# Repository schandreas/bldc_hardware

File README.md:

This is a fork of Benjamin Vedders Open Source VESC project: https://github.com/vedderb/bldc-hardware

## Goals: 
The original Vesc design is very good for the things it wants to do. I want to do different things and still be able to use the same firmware. So I made this version.

The idea was that I only wanted to drive very weak motors. So this version is cheap and not that good. :man_shrugging:

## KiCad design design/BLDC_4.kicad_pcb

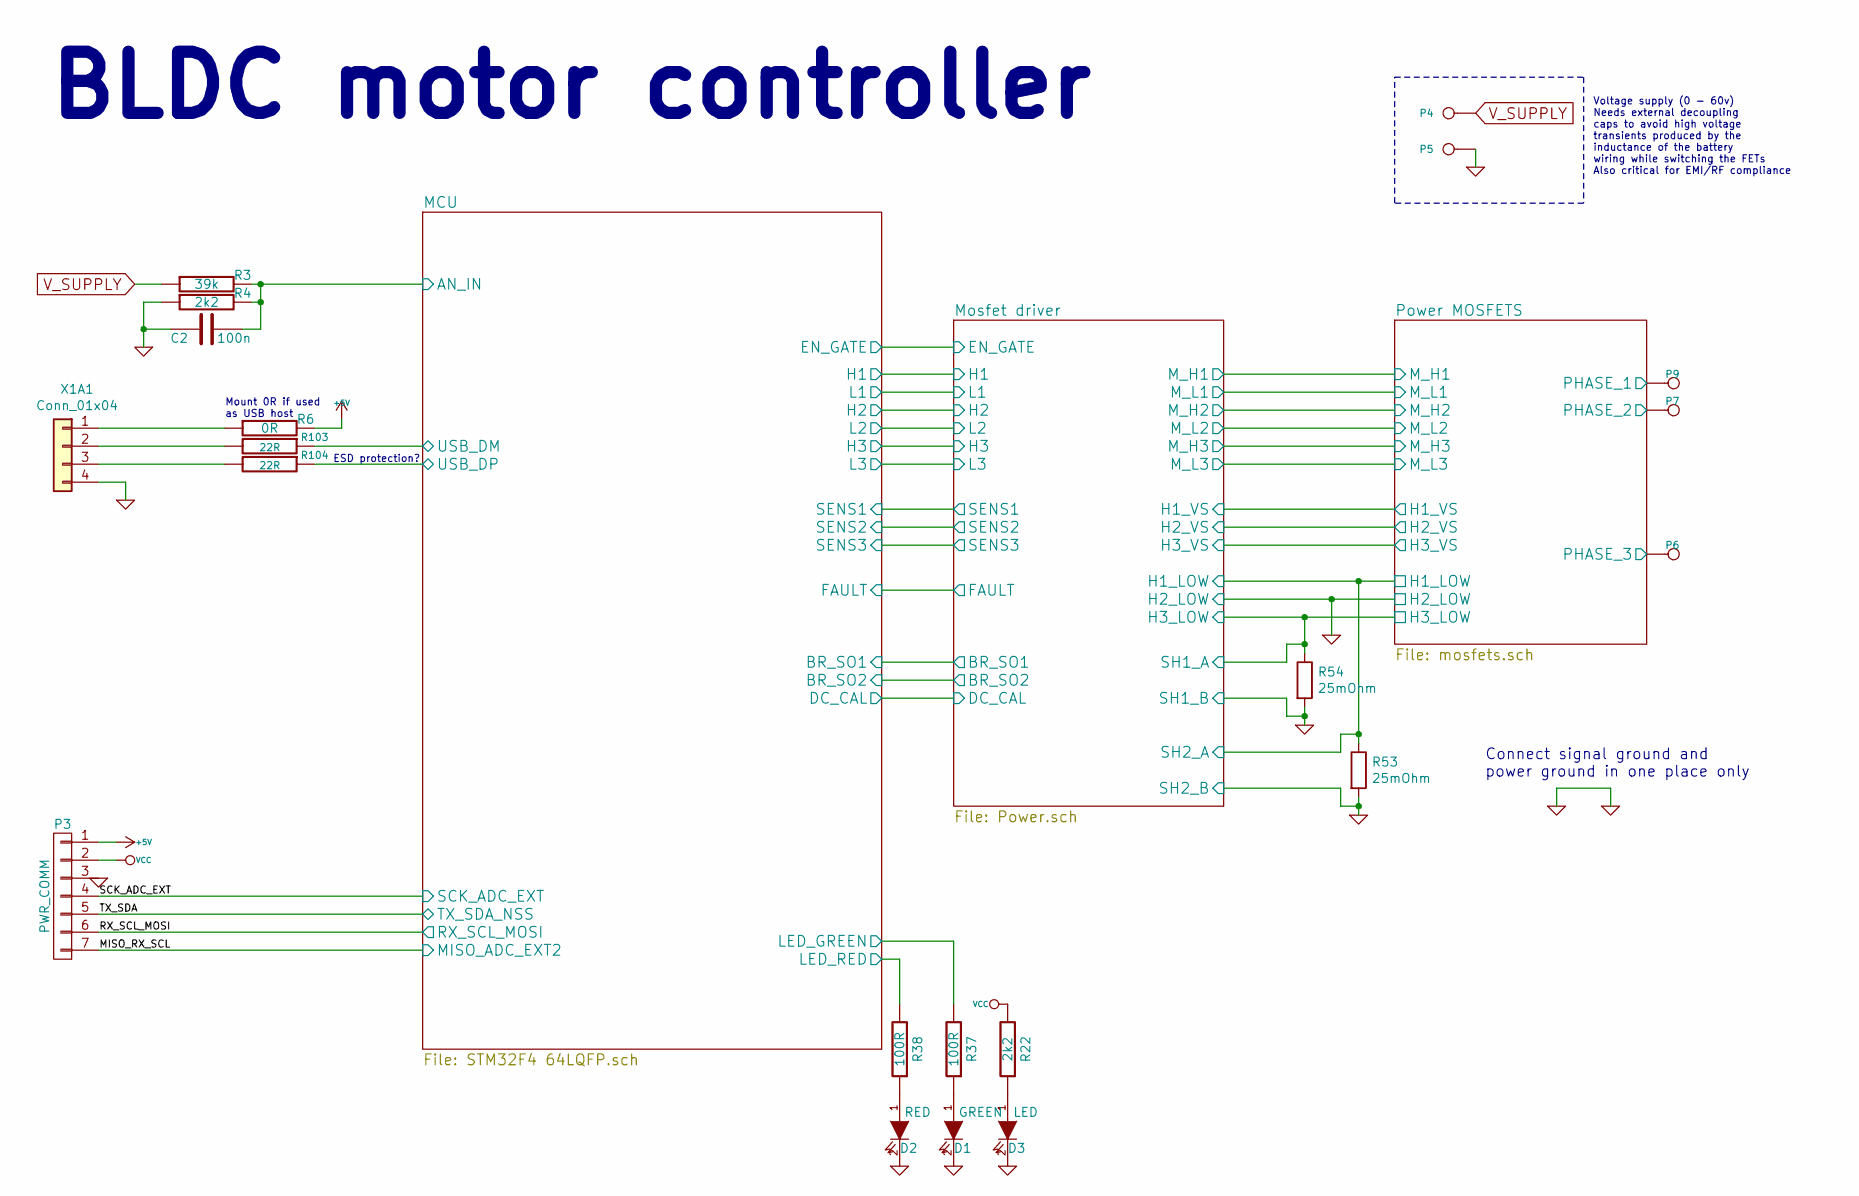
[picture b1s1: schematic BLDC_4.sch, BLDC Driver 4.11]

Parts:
C2: 100n; C_0603_1608Metric_Pad1.05x0.95mm_HandSolder
D1: GREEN; LED_0603_1608Metric
D2: RED; LED_0603_1608Metric
D3: LED; LED_0603_1608Metric
P3: PWR_COMM; JST_PH_B7B-PH-K_1x07_P2.00mm_Vertical
P4: IN+; 1PAD_4x5mm
P5: IN-; 1PAD_4x5mm
P6: MOTOR1; 1PAD_4x5mm
P7: MOTOR2; 1PAD_4x5mm
P9: MOTOR3; 1PAD_4x5mm
R3: 39k; R_0603_1608Metric
R4, R22: 2k2; R_0603_1608Metric
R6: 0R; R_0603_1608Metric
R37, R38: 100R; R_0603_1608Metric
R53, R54: 25mOhm; R_0612_1632Metric
R103, R104: 22R; R_0603_1608Metric
X1A1: Conn_01x04; PinHeader_1x04_P2.54mm_Vertical

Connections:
+5V: P3.1, R6.2; also elsewhere on the board
/MCU/AN_IN: C2.2, R3.2, R4.2; also elsewhere on the board
/MCU/LED_GREEN: R37.2; also elsewhere on the board
/MCU/LED_RED: R38.2; also elsewhere on the board
/MCU/USB_DM: R103.1; also elsewhere on the board
/MCU/USB_DP: R104.1; also elsewhere on the board
/MISO_RX_SCL: P3.7; also elsewhere on the board
/Mosfet driver/H1_LOW: R53.1; also elsewhere on the board
/Mosfet driver/H1_VS: P9.1; also elsewhere on the board
/Mosfet driver/H2_VS: P7.1; also elsewhere on the board
/Mosfet driver/H3_LOW: R54.1; also elsewhere on the board
/Mosfet driver/H3_VS: P6.1; also elsewhere on the board
/RX_SCL_MOSI: P3.6; also elsewhere on the board
/SCK_ADC_EXT: P3.4; also elsewhere on the board
/TX_SDA: P3.5; also elsewhere on the board
GND: C2.1, D1.2 (K), D2.2 (K), D3.2 (K), P3.3, P5.1, R4.1, R53.2, R54.2, X1A1.4; also elsewhere on the board
unnamed: D1.1 (A), R37.1
unnamed: D2.1 (A), R38.1
unnamed: D3.1 (A), R22.1
unnamed: R6.1, X1A1.1
unnamed: R103.2, X1A1.2
unnamed: R104.2, X1A1.3
VCC: P3.2, R22.2; also elsewhere on the board
V_SUPPLY: P4.1, R3.1; also elsewhere on the board

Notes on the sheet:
Mount 0R if used as USB host
ESD protection?
BLDC motor controller
Voltage supply (0 - 60v) Needs external decoupling caps to avoid high voltage transients produced by the inductance of the battery wiring while switching the FETs Also critical for EMI/RF compliance
Connect signal ground and power ground in one place only

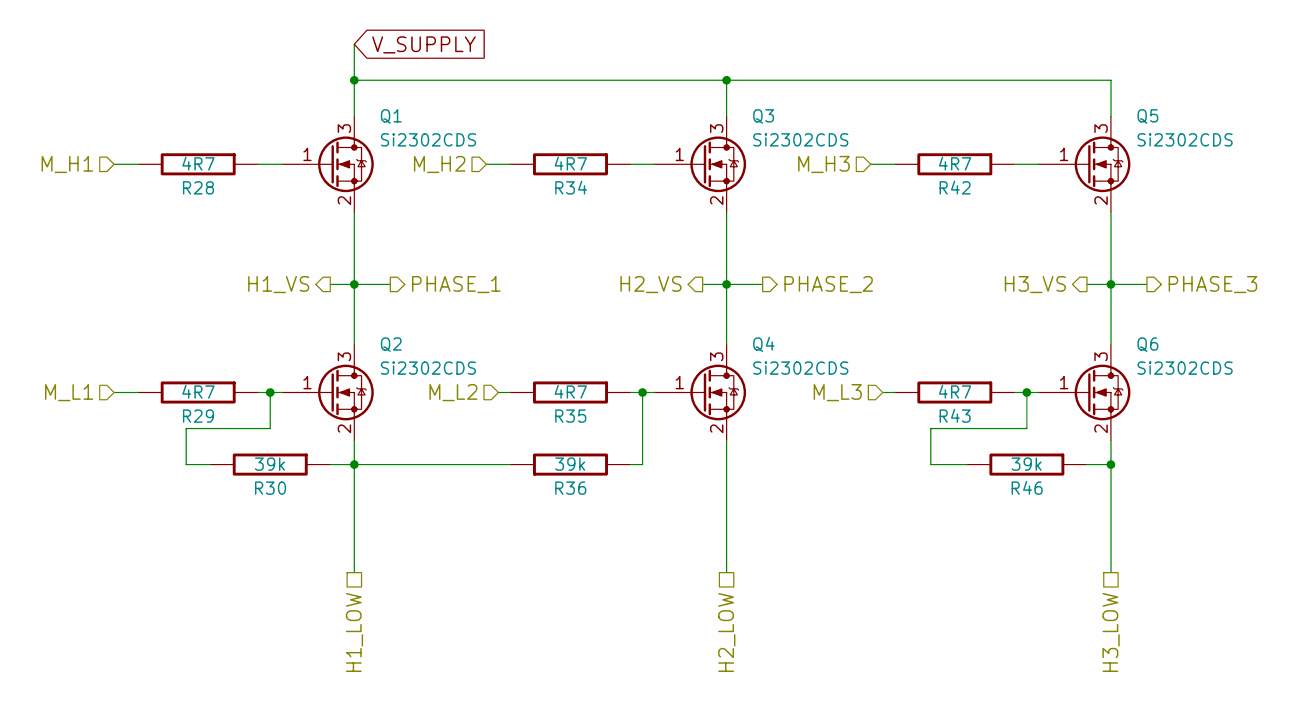
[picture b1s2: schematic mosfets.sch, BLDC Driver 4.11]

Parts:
Q1, Q2, Q3, Q4, Q5, Q6: Si2302CDS; SOT-23
R28, R29, R34, R35, R42, R43: 4R7; R_0603_1608Metric
R30, R36, R46: 39k; R_0603_1608Metric

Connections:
/Mosfet driver/H1_LOW: Q2.2 (S), R30.1, R36.1; also elsewhere on the board
/Mosfet driver/H1_VS: Q1.2 (S), Q2.3 (D); also elsewhere on the board
/Mosfet driver/H2_VS: Q3.2 (S), Q4.3 (D); also elsewhere on the board
/Mosfet driver/H3_LOW: Q6.2 (S), R46.1; also elsewhere on the board
/Mosfet driver/H3_VS: Q5.2 (S), Q6.3 (D); also elsewhere on the board
/Mosfet driver/M_H1: R28.2; also elsewhere on the board
/Mosfet driver/M_H2: R34.2; also elsewhere on the board
/Mosfet driver/M_H3: R42.2; also elsewhere on the board
/Mosfet driver/M_L1: R29.2; also elsewhere on the board
/Mosfet driver/M_L2: R35.2; also elsewhere on the board
/Mosfet driver/M_L3: R43.2; also elsewhere on the board
GND: Q4.2 (S); also elsewhere on the board
unnamed: Q1.1 (G), R28.1
unnamed: Q2.1 (G), R29.1, R30.2
unnamed: Q3.1 (G), R34.1
unnamed: Q4.1 (G), R35.1, R36.2
unnamed: Q5.1 (G), R42.1
unnamed: Q6.1 (G), R43.1, R46.2
V_SUPPLY: Q1.3 (D), Q3.3 (D), Q5.3 (D); also elsewhere on the board

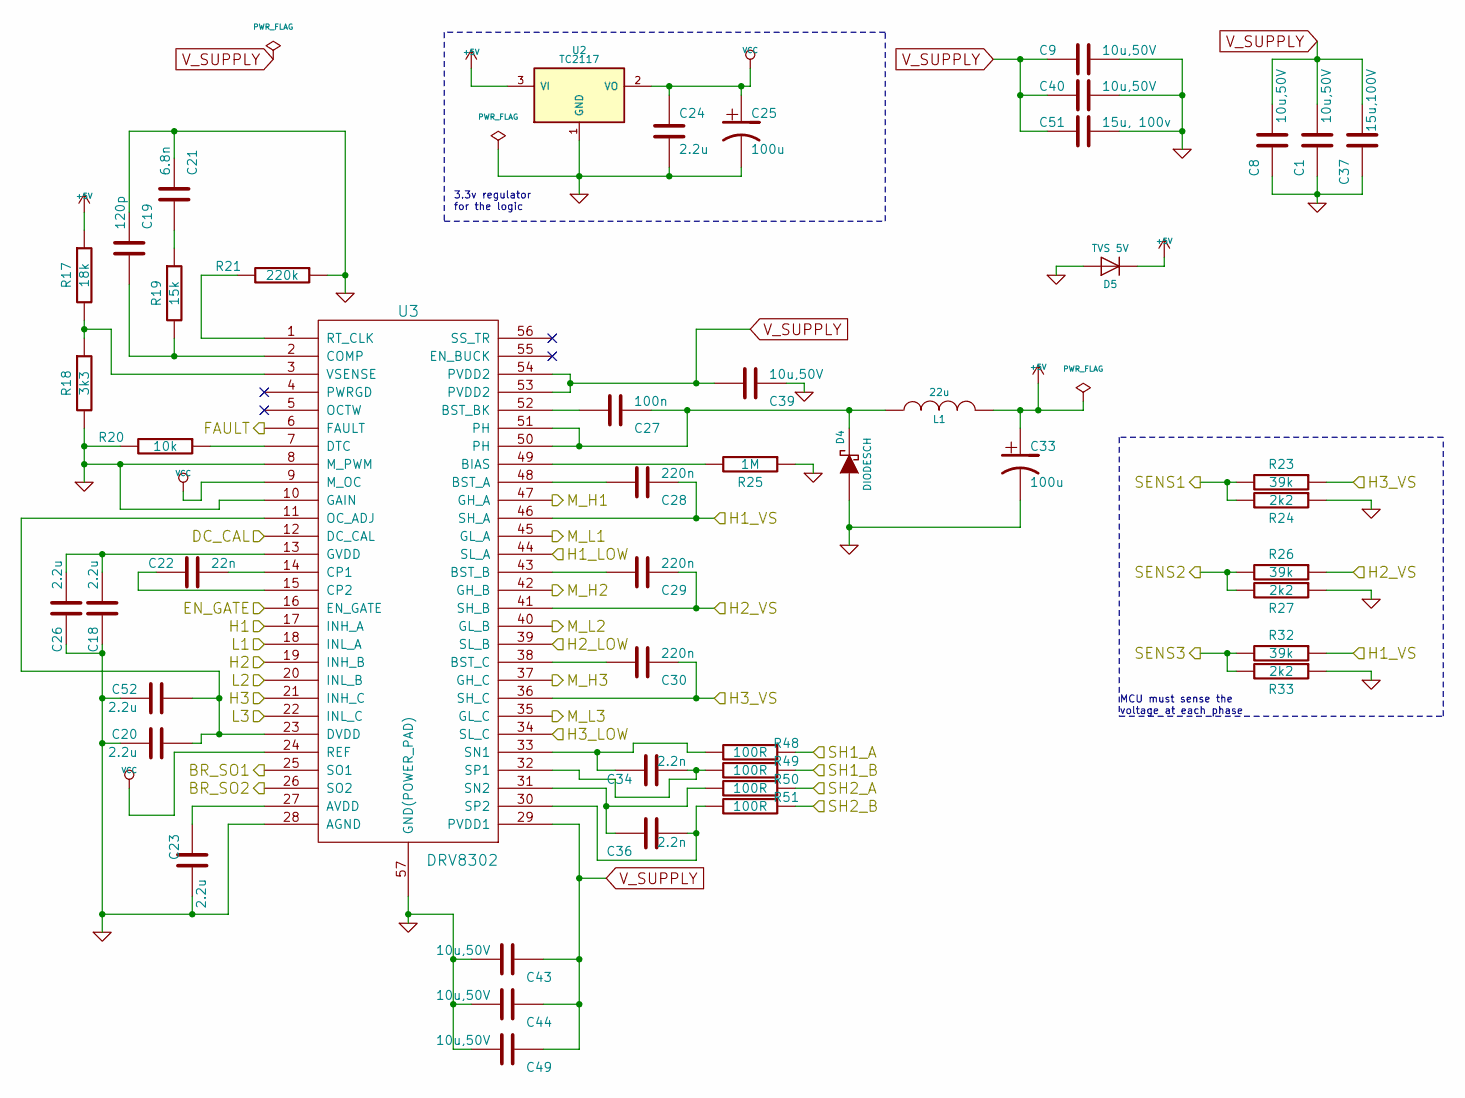
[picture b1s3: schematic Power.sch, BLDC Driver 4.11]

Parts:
C1, C8, C9, C39, C40, C43, C44, C49: 10u,50V; C_1206_3216Metric
C18, C20, C23, C24, C26, C52: 2.2u; C_0603_1608Metric_Pad1.05x0.95mm_HandSolder
C19: 120p; C_0603_1608Metric_Pad1.05x0.95mm_HandSolder
C21: 6.8n; C_0603_1608Metric_Pad1.05x0.95mm_HandSolder
C22: 22n; C_0603_1608Metric_Pad1.05x0.95mm_HandSolder
C25, C33: 100u; CP_EIA-3528-21_Kemet-B
C27: 100n; C_0603_1608Metric_Pad1.05x0.95mm_HandSolder
C28, C29, C30: 220n; C_0603_1608Metric_Pad1.05x0.95mm_HandSolder
C34, C36: 2.2n; C_0603_1608Metric_Pad1.05x0.95mm_HandSolder
C37: 15u,100V; C_2220_5650Metric
C51: 15u, 100v; C_2220_5650Metric
D4: DIODESCH; D_SMA_Handsoldering
D5: TVS 5V; D_SMA_Handsoldering
L1: 22u; inductor_smd_8x5mm
R17: 18k; R_0603_1608Metric
R18: 3k3; R_0603_1608Metric
R19: 15k; R_0603_1608Metric
R20: 10k; R_0603_1608Metric
R21: 220k; R_0603_1608Metric
R23, R26, R32: 39k; R_0603_1608Metric
R24, R27, R33: 2k2; R_0603_1608Metric
R25: 1M; R_0603_1608Metric
R48, R49, R50, R51: 100R; R_0603_1608Metric
U2: TC2117; SOT-223-3_TabPin2
U3: DRV8302; HTSSOP-56-1EP_6.1x14mm_P0.5mm_EP3.61x6.35mm

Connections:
+5V: C33.1, D5.1 (K), L1.2, R17.1, U2.3 (VI); also elsewhere on the board
/MCU/BR_SO1: U3.25 (SO1); also elsewhere on the board
/MCU/BR_SO2: U3.26 (SO2); also elsewhere on the board
/MCU/DC_CAL: U3.12 (DC_CAL); also elsewhere on the board
/MCU/EN_GATE: U3.16 (EN_GATE); also elsewhere on the board
/MCU/FAULT: U3.6 (FAULT); also elsewhere on the board
/MCU/H1: U3.17 (INH_A); also elsewhere on the board
/MCU/H2: U3.19 (INH_B); also elsewhere on the board
/MCU/H3: U3.21 (INH_C); also elsewhere on the board
/MCU/L1: U3.18 (INL_A); also elsewhere on the board
/MCU/L2: U3.20 (INL_B); also elsewhere on the board
/MCU/L3: U3.22 (INL_C); also elsewhere on the board
/MCU/SENS1: R23.2, R24.2; also elsewhere on the board
/MCU/SENS2: R26.2, R27.2; also elsewhere on the board
/MCU/SENS3: R32.2, R33.2; also elsewhere on the board
/Mosfet driver/H1_LOW: R50.1, U3.44 (SL_A); also elsewhere on the board
/Mosfet driver/H1_VS: C28.1, R32.1, U3.46 (SH_A); also elsewhere on the board
/Mosfet driver/H2_VS: C29.1, R26.1, U3.41 (SH_B); also elsewhere on the board
/Mosfet driver/H3_LOW: R48.1, U3.34 (SL_C); also elsewhere on the board
/Mosfet driver/H3_VS: C30.1, R23.1, U3.36 (SH_C); also elsewhere on the board
/Mosfet driver/M_H1: U3.47 (GH_A); also elsewhere on the board
/Mosfet driver/M_H2: U3.42 (GH_B); also elsewhere on the board
/Mosfet driver/M_H3: U3.37 (GH_C); also elsewhere on the board
/Mosfet driver/M_L1: U3.45 (GL_A); also elsewhere on the board
/Mosfet driver/M_L2: U3.40 (GL_B); also elsewhere on the board
/Mosfet driver/M_L3: U3.35 (GL_C); also elsewhere on the board
GND: C1.1, C8.1, C9.1, C18.2, C19.1, C20.1, C21.1, C23.1, C24.2, C25.2, C26.2, C33.2, C37.1, C39.1, C40.1, C43.2, C44.2, C49.2, C51.1, C52.1, D4.1 (A), D5.2 (A), R18.2, R20.2, R21.1, R24.1, R25.1, R27.1, R33.1, R49.1, R51.1, U2.1 (GND), U3.8 (M_PWM), U3.10 (GAIN), U3.28 (AGND), U3.39 (SL_B), U3.57 (GND(POWER_PAD)); also elsewhere on the board
unnamed: C18.1, C26.1, U3.13 (GVDD)
unnamed: C19.2, R19.2, U3.2 (COMP)
unnamed: C20.2, C52.2, U3.11 (OC_ADJ), U3.23 (DVDD)
unnamed: C21.2, R19.1
unnamed: C22.1, U3.14 (CP1)
unnamed: C22.2, U3.15 (CP2)
unnamed: C23.2, U3.27 (AVDD)
unnamed: C27.1, D4.2 (K), L1.1, U3.50 (PH), U3.51 (PH)
unnamed: C27.2, U3.52 (BST_BK)
unnamed: C28.2, U3.48 (BST_A)
unnamed: C29.2, U3.43 (BST_B)
unnamed: C30.2, U3.38 (BST_C)
unnamed: C34.1, R48.2, U3.33 (SN1)
unnamed: C34.2, R49.2, U3.32 (SP1)
unnamed: C36.1, R50.2, U3.31 (SN2)
unnamed: C36.2, R51.2, U3.30 (SP2)
unnamed: R17.2, R18.1, U3.3 (VSENSE)
unnamed: R20.1, U3.7 (DTC)
unnamed: R21.2, U3.1 (RT_CLK)
unnamed: R25.2, U3.49 (BIAS)
VCC: C24.1, C25.1, U2.2 (VO), U3.9 (M_OC), U3.24 (REF); also elsewhere on the board
V_SUPPLY: C1.2, C8.2, C9.2, C37.2, C39.2, C40.2, C43.1, C44.1, C49.1, C51.2, U3.29 (PVDD1), U3.53 (PVDD2), U3.54 (PVDD2); also elsewhere on the board

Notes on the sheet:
MCU must sense the voltage at each phase
3.3v regulator for the logic

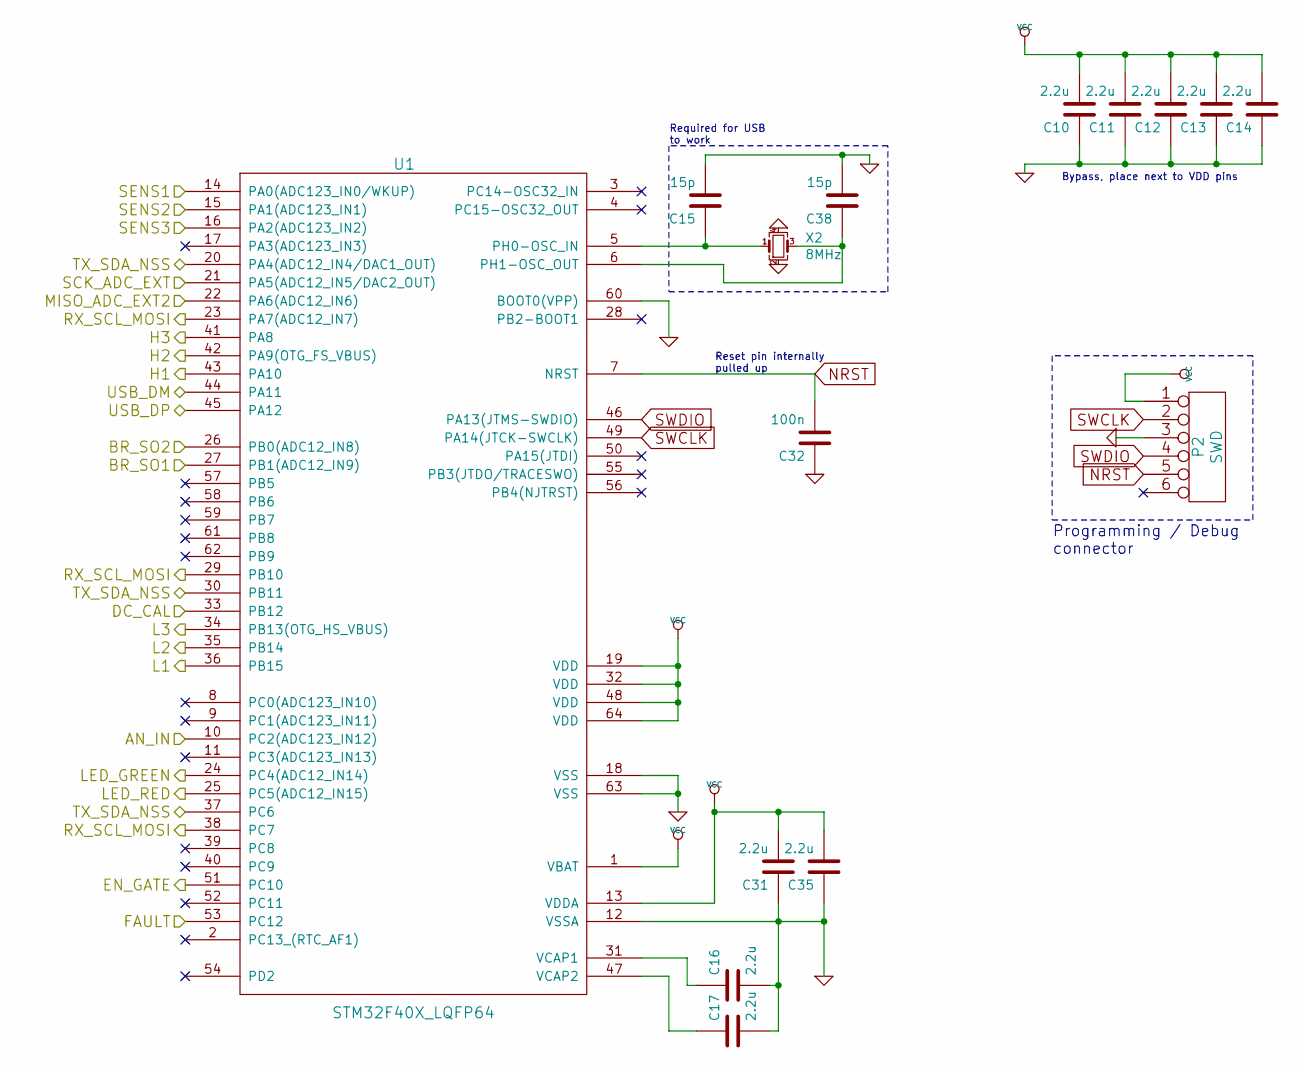
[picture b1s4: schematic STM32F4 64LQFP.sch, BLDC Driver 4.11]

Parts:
C10, C11, C12, C13, C14, C16, C17, C31, C35: 2.2u; C_0603_1608Metric
C15, C38: 15p; C_0603_1608Metric
C32: 100n; C_0603_1608Metric
P2: SWD; JST_PH_B6B-PH-K_1x06_P2.00mm_Vertical
U1: STM32F40X_LQFP64; LQFP-64_10x10mm_P0.5mm
X2: 8MHz; Crystal_SMD_Abracon_ABM3B-4Pin_5.0x3.2mm

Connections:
/MCU/AN_IN: U1.10 (PC2(ADC123_IN12)); also elsewhere on the board
/MCU/BR_SO1: U1.27 (PB1(ADC12_IN9)); also elsewhere on the board
/MCU/BR_SO2: U1.26 (PB0(ADC12_IN8)); also elsewhere on the board
/MCU/DC_CAL: U1.33 (PB12); also elsewhere on the board
/MCU/EN_GATE: U1.51 (PC10); also elsewhere on the board
/MCU/FAULT: U1.53 (PC12); also elsewhere on the board
/MCU/H1: U1.43 (PA10); also elsewhere on the board
/MCU/H2: U1.42 (PA9(OTG_FS_VBUS)); also elsewhere on the board
/MCU/H3: U1.41 (PA8); also elsewhere on the board
/MCU/L1: U1.36 (PB15); also elsewhere on the board
/MCU/L2: U1.35 (PB14); also elsewhere on the board
/MCU/L3: U1.34 (PB13(OTG_HS_VBUS)); also elsewhere on the board
/MCU/LED_GREEN: U1.24 (PC4(ADC12_IN14)); also elsewhere on the board
/MCU/LED_RED: U1.25 (PC5(ADC12_IN15)); also elsewhere on the board
/MCU/SENS1: U1.14 (PA0(ADC123_IN0/WKUP)); also elsewhere on the board
/MCU/SENS2: U1.15 (PA1(ADC123_IN1)); also elsewhere on the board
/MCU/SENS3: U1.16 (PA2(ADC123_IN2)); also elsewhere on the board
/MCU/USB_DM: U1.44 (PA11); also elsewhere on the board
/MCU/USB_DP: U1.45 (PA12); also elsewhere on the board
/MISO_RX_SCL: U1.22 (PA6(ADC12_IN6)); also elsewhere on the board
/RX_SCL_MOSI: U1.23 (PA7(ADC12_IN7)), U1.29 (PB10), U1.38 (PC7); also elsewhere on the board
/SCK_ADC_EXT: U1.21 (PA5(ADC12_IN5/DAC2_OUT)); also elsewhere on the board
/TX_SDA: U1.20 (PA4(ADC12_IN4/DAC1_OUT)), U1.30 (PB11), U1.37 (PC6); also elsewhere on the board
GND: C10.1, C11.1, C12.1, C13.1, C14.1, C15.2, C16.2, C17.2, C31.1, C32.1, C35.1, C38.2, P2.3, U1.12 (VSSA), U1.18 (VSS), U1.60 (BOOT0(VPP)), U1.63 (VSS), X2.2, X2.4; also elsewhere on the board
NRST: C32.2, P2.5, U1.7 (NRST)
unnamed: C15.1, U1.5 (PH0-OSC_IN), X2.1
unnamed: C16.1, U1.31 (VCAP1)
unnamed: C17.1, U1.47 (VCAP2)
unnamed: C38.1, U1.6 (PH1-OSC_OUT), X2.3
SWCLK: P2.2, U1.49 (PA14(JTCK-SWCLK))
SWDIO: P2.4, U1.46 (PA13(JTMS-SWDIO))
VCC: C10.2, C11.2, C12.2, C13.2, C14.2, C31.2, C35.2, P2.1, U1.1 (VBAT), U1.13 (VDDA), U1.19 (VDD), U1.32 (VDD), U1.48 (VDD), U1.64 (VDD); also elsewhere on the board

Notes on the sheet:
Programming / Debug connector
Reset pin internally pulled up
Required for USB to work
Bypass, place next to VDD pins

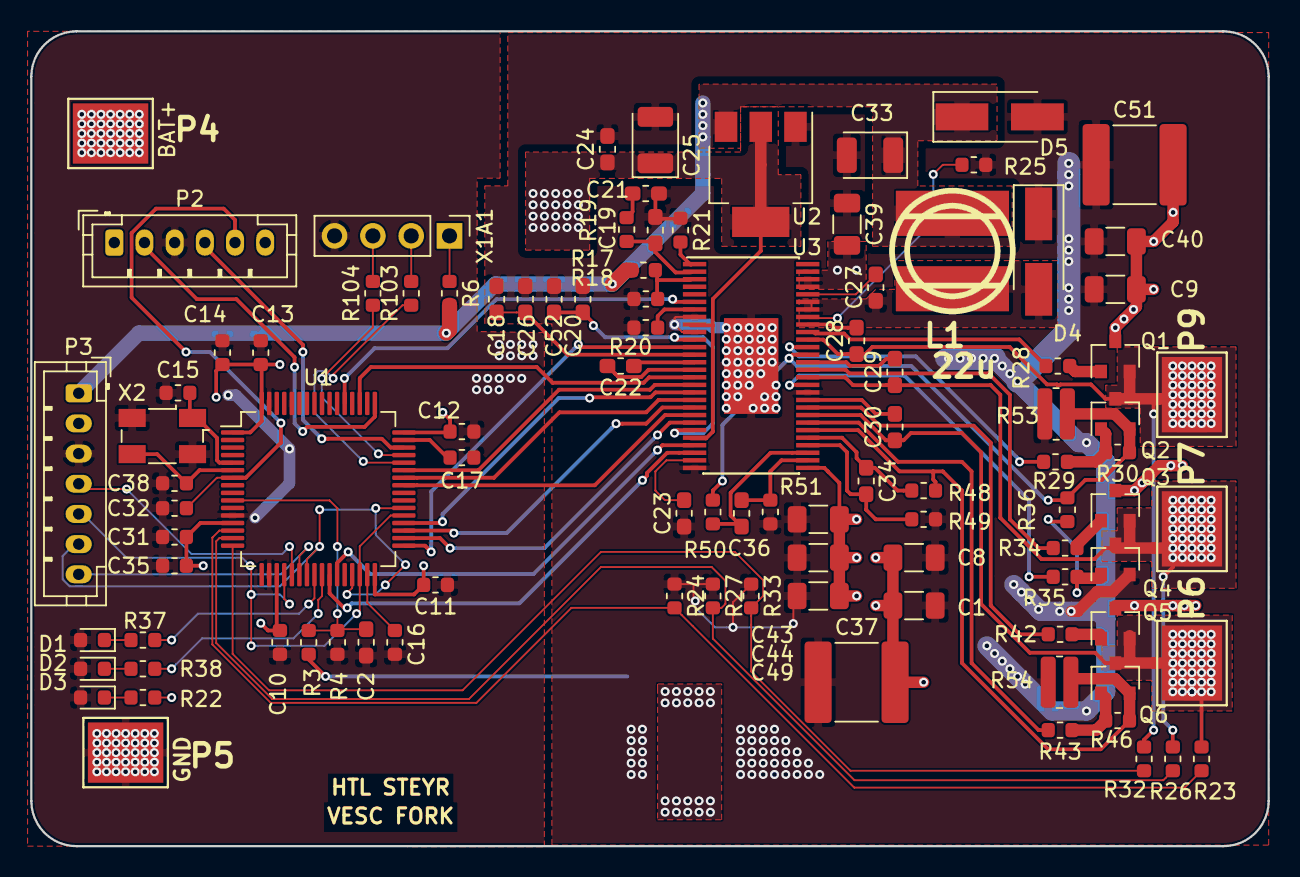
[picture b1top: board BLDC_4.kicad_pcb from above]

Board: 2 copper layers, 82.0 x 54.0 mm, 99 parts (0 on the bottom side), 77 nets.

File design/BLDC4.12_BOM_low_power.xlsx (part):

Part | Value | Package | Description | Qty | Place (YES/NO) | Distributor | Order Number | Comment | single price | multi price | link |  |  |  |  |  |  |  |  |  |  |  | LCSC
U1 |  | LQFP-64 | STM32F405RGT6 MCU | 1 | YES | RS | 746-8217 |  | 9.24 | 9.24 | https://at.rs-online.com/web/p/mikrocontroller/7468217/ |  |  |  |  |  |  |  |  |  |  |  | https://lcsc.com/product-detail/ST-Microelectronics_STMicroe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
U2 |  | SOT-223-3 | VREG | 1 | YES | RS | 823-4434 | moq 10 | 0.63300000000000001 | 0.63300000000000001 | https://at.rs-online.com/web/p/ldo-spannungsregler/8234434/ |  |  |  |  |  |  |  |  |  |  |  | https://lcsc.com/product-detail/Low-Dropout-Regulators-LDO_M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
U3 |  | HTSSOP-56-PP | MOSFET Driver | 1 | YES | RS | 762-0421 |  | 5.45 | 5.45 | https://at.rs-online.com/web/p/motor-treiber-ics/7620421/ |  |  |  |  |  |  |  |  |  |  |  | https://lcsc.com/product-detail/MOS-Drivers_TI_DRV8302DCA_DR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
L1 |  | inductor_smd_8x5mm | Power Inductor | 1 | YES | MOUSER | 652-SDR0805-220ML |  | 0.45 | 0.45 | https://www.mouser.at/ProductDetail/Bourns/SDR0805-220ML?qs=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
X1 |  | Conn_1x04 | Pinheader 1x04 2.54mm | 1 | YES | RS | 720-1310 | moq 10 | 0.22600000000000001 | 0.22600000000000001 | https://at.rs-online.com/web/p/leiterplatten-header/7201310/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
X2 | 8MHz | Crystal_5x3mm | Crystal 8MHz, 10PPM | 1 | YES | MOUSER | 815-ABM3B-8.0-10-1UT |  | 0.621 | 0.621 | https://www.mouser.at/ProductDetail/ABRACON/ABM3B-8000MHZ-10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 |  |  |  |  |  |  |  |  |  |  |  | https://lcsc.com/product-detail/Power-Inductors_BOURNS_SDR08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
Q1-Q6 | Si2302CDS | SOT-23 | MOSFET 20V 3A | 6 | YES | Farnell | 1684049 |  | 0.192 | 1.1520000000000001 | https://at.farnell.com/vishay/si2302cds-t1-ge3/mosfet-n-kana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
R53,R54 | 25mOhm | SMD-0612 | Shunt 25mOhm | 2 | YES | MOUSER | 652-CRK0612-FZ-R001E |  | 0.53 | 1.06 | https://www.mouser.at/ProductDetail/Bourns/CRK0612-FZ-R001E?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
D5 | 5V | DO-214AC-2 | TVS diode 5V | 1 | YES | MOUSER | 576-SMAJ5.0A |  | 0.36899999999999999 | 0.36899999999999999 | https://www.mouser.at/ProductDetail/Littelfuse/SMAJ50A?qs=%2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
D4 | 60V 2A | SOD-123W-2 | Shottky 60V 2A | 1 | YES | MOUSER | 771-PMEG6020ER-115 | Voltage and current important | 0.315 | 0.315 | https://www.mouser.at/ProductDetail/Nexperia/PMEG6020ER115?q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
C25,C33 | 100uF, 6.3V | c_tant_B | CAP 100u, 6.3V | 2 | YES | RS | 136-4122 | Voltage important, moq 25 | 0.442 | 0.88400000000000001 | https://at.rs-online.com/web/p/tantal-elektrolytkondensator/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
C1,C8,C9,C39,C40,C43,C44,C49 | 10uF 50V | SMD1206 | CAP 10u, 50V, 1206 | 8 | YES | MOUSER | 963-UMK316BBJ106ML-T | Voltage important, moq 10 | 0.31 | 2.48 | https://www.mouser.at/ProductDetail/Taiyo-Yuden/UMK316BBJ106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
C37,C51 | 15uF, 100V | SMD-2220 | CAP 15u, 100V, 2220 | 2 | YES | MOUSER | 810-CGA9P3X7S2A156M | Voltage important | 3.24 | 6.48 | https://www.mouser.at/ProductDetail/TDK/CGA9P3X7S2A156M250KB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
C2,C27,C32 | 100nF, 50V | SMD-0603 | CAP 100n, 50V, 0603 | 3 | YES | MOUSER | 581-06035C104JAT2A | Voltage important | 0.13500000000000001 | 0.40500000000000003 | https://www.mouser.at/ProductDetail/AVX/06035C104JAT2A?qs=%2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
C28,C29,C30 | 220nF,25V | SMD-0603 | CAP 220n, 25V, 0603 | 3 | YES | MOUSER | 963-TMK107B7224KA-T | Voltage important | 9.9000000000000005E-2 | 0.29700000000000004 | https://www.mouser.at/ProductDetail/Taiyo-Yuden/TMK107B7224K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
C24,C10,C11,C12,C13,C14,C16,C17,C18,C20,C23,C26,C31,C35,C52 | 2.2uF, 16V | SMD-0603 | CAP 2.2u, 16V, 0603 | 15 | YES | MOUSER | 810-C1608X5R1C225M | Voltage important, moq 10 | 0.17100000000000001 | 2.5650000000000004 | https://www.mouser.at/ProductDetail/TDK/C1608X5R1C225M080AB?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
P3 |  | MICRO_JST_7 | Micro-JST 7PIN 2mm | 1 | YES | Conrad | 740103 - 62 | Can be found on ebay | 0.44 | 0.44 | https://www.conrad.at/de/p/jst-einbau-stiftleiste-standard-p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 |  |  |  |  |  |  |  |  |  |  |  | https://lcsc.com/product-detail/Wire-To-Board-Wire-To-Wire-C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
P2 |  | MICRO_JST_6 | Micro-JST 6PIN 2mm | 1 | YES | Conrad | 741271 - 62 | Can be found on ebay | 0.69 | 0.69 | https://www.conrad.at/de/p/jst-einbau-stiftleiste-standard-p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 |  |  |  |  |  |  |  |  |  |  |  | https://lcsc.com/product-detail/Wire-To-Board-Wire-To-Wire-C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
C34, C36 | 2.2nF, 50V | SMD-0603 | CAP 2.2n, 50V, 0603 | 2 | YES | Farnell | 2409039 | moq 10 | 4.07E-2 | 8.14E-2 | https://at.farnell.com/kemet/c0603c222j5ractu/kondensator-22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 |  |  |  |  |  |  |  |  |  |  |  | https://lcsc.com/product-detail/Multilayer-Ceramic-Capacitor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
C15,C38 | 15pF, 100V | SMD-0603 | CAP 15p, 100V, 0603 | 2 | YES | MOUSER | 81-GRM1885C2A150JA01 |  | 9.9000000000000005E-2 | 0.19800000000000001 | https://www.mouser.at/ProductDetail/Murata-Electronics/GRM18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 |  |  |  |  |  |  |  |  |  |  |  | https://lcsc.com/product-detail/Multilayer-Ceramic-Capacitor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
C19 | 120pF, 50V | SMD-0603 | CAP 120p, 50V, 0603 | 1 | YES | MOUSER | 81-GRM39C121J50 |  | 0.13500000000000001 | 0.13500000000000001 | https://www.mouser.at/ProductDetail/Murata-Electronics/GRM18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 |  |  |  |  |  |  |  |  |  |  |  | https://lcsc.com/product-detail/Multilayer-Ceramic-Capacitor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
C21 | 6.8nF, 50V | SMD-0603 | CAP 6.8n, 50V, 0603 | 1 | YES | Farnell | 1759100 | moq 10 | 1.4200000000000001E-2 | 1.4200000000000001E-2 | https://at.farnell.com/multicomp/mc0603b682k500ct/kondensato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 |  |  |  |  |  |  |  |  |  |  |  | https://lcsc.com/product-detail/Multilayer-Ceramic-Capacitor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
C22 | 22nF, 50V | SMD-0603 | CAP 22n, 50V, 0603 | 1 | YES | Farnell | 1414625 | moq 10 | 4.87E-2 | 4.87E-2 | https://at.farnell.com/kemet/c0603c223k5ractu/kondensator-0-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 |  |  |  |  |  |  |  |  |  |  |  | https://lcsc.com/product-detail/Multilayer-Ceramic-Capacitor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
D1 |  | SMD-0603 | LED Green, 0603 | 1 | YES | MOUSER | 859-LTST-C191KGKT |  | 0.23400000000000001 | 0.23400000000000001 | https://www.mouser.at/ProductDetail/Lite-On/LTST-C191KGKT?qs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 |  |  |  |  |  |  |  |  |  |  |  | https://lcsc.com/product-detail/Light-Emitting-Diodes-LED_SM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
D2 |  | SMD-0603 | LED Red, 0603 | 1 | YES | MOUSER | 859-LTST-C191KRKT |  | 0.23400000000000001 | 0.23400000000000001 | https://www.mouser.at/ProductDetail/Lite-On/LTST-C191KRKT?qs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 |  |  |  |  |  |  |  |  |  |  |  | https://lcsc.com/product-detail/Light-Emitting-Diodes-LED_SM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
D3 |  | SMD-0603 | LED Blue, 0603 | 1 | YES | MOUSER | 720-LBQ39GN1P1351 |  | 0.38700000000000001 | 0.38700000000000001 | https://www.mouser.at/ProductDetail/OSRAM-Opto-Semiconductor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
R28,R29,R34,R35,R42,R43 | 4.7ohm | SMD-0603 | R 4.7ohm, 0603 | 6 | YES | MOUSER | 660-RK73H1JTTD4R70F | moq 10 | 2.1000000000000001E-2 | 0.126 | https://www.mouser.at/ProductDetail/KOA-Speer/RK73H1JTTD4R70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 |  |  |  |  |  |  |  |  |  |  |  | https://lcsc.com/product-detail/Chip-Resistor-Surface-Mount_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
R37,R38,R48-R51,R401 | 100ohm | SMD-0603 | R 100ohm, 0603 | 6 | YES | Farnell | 2074165 | moq 10 | 9.4999999999999998E-3 | 5.6999999999999995E-2 | https://at.farnell.com/multicomp/mcsr06x1000ftl/keramikwider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 |  |  |  |  |  |  |  |  |  |  |  | https://lcsc.com/product-detail/Chip-Resistor-Surface-Mount_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
R4,R5,R11,R12,R13,R22,R24,R27,R33 | 2.2kOhm | SMD-0603 | R 2.2k, 0603 | 5 | YES | Farnell | 2074215 | moq 10 | 9.7000000000000003E-3 | 4.8500000000000001E-2 | https://at.farnell.com/multicomp/mcsr06x2201ftl/keramikwider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 |  |  |  |  |  |  |  |  |  |  |  | https://lcsc.com/product-detail/Chip-Resistor-Surface-Mount_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
R18 | 3.3kOhm | SMD-0603 | R 3.3k, 0603 | 1 | YES | MOUSER | 660-RK73H1JTTD3301F |  | 0.10100000000000001 | 0.10100000000000001 | https://www.mouser.at/ProductDetail/KOA-Speer/RK73H1JTTD3301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 |  |  |  |  |  |  |  |  |  |  |  | https://lcsc.com/product-detail/Chip-Resistor-Surface-Mount_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
R20 | 10kOhm | SMD-0603 | R 10k, 0603 | 1 | YES | Farnell | 2074167 | moq 10 | 1.41E-2 | 1.41E-2 | https://at.farnell.com/multicomp/mcsr06x1002ftl/keramikwider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 |  |  |  |  |  |  |  |  |  |  |  | https://lcsc.com/product-detail/Chip-Resistor-Surface-Mount_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

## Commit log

2019-11-08 Version 0.1 :godmode:
2019-11-08 Update readme and remove datasheets :^)
2019-11-15 Removing and Redoing almost all auxilliary files
    Good ol' Benjamin made a lot of niftly little side files to make the schematic and layout easier to view. Things like pdfs and the like. The ones we still needed were kept and changed, the rest were 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
2019-11-15 Fixing ERC Errors :+1:
    Turns out you need to mark pins as not connected. Who knew? Not me :sunglasses:
2019-11-15 Nailing down the connecting pads with vias and Connecting the Filter Caps better
    Turns out you CAN put lipstick on a pig :+1:
2019-11-15 Reworked Silkscreen :suspect:
    It no longer looks like a pile of :shit:
2019-11-15 Rounded Corners on the PCB to take the edge of things
    :see_no_evil:
2019-11-19 Removed trash backup folder
2019-11-29 tiny silkscreen change
2019-11-29 Increasing current carrying capability
    Added more vias and dedicated polygons to output stage.
2019-11-29 widened thermals
2019-12-06 Strengthening fills for output stage. Adding GND Fill
    More to come :godmode:
2019-12-13 Rework Board to fatten up supply
    :snake: sneaky stuff :snake:
2019-12-13 Infill change
2020-01-10 Added BOM and reworked component naming to be inline with old VESC names
    :^)
2020-02-14 Fixed Crystal connection and footprint
2020-03-13 v0.2 Bug fixes and improvements
    Fixed wrong GND net near shunts
    Seperated GND and PWRGND
    Added another GND net for capacitors near output stage
2020-03-13 fixes silkscreen. Updated Gerber
2020-03-13 Updated BOM
